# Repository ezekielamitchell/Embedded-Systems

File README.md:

# REDHAWK ESP32 Robot

Custom PCB-based robot designed and built for the Seattle University Embedded Systems & Design course. The board centers on an ESP32 microcontroller and includes motor drive, quadrature encoders, distance sensing, line following, ambient light sensing, audio output, and Wi-Fi. This repository contains the full KiCad hardware design, power-on functional test firmware, and supporting documentation.

---

## Repository Structure

```
Embedded-Systems/
├── Mitchel_Ezekiel_Robot/       # KiCad PCB and schematic project
├── PowerOn_Functional_Test/     # PlatformIO firmware — hardware self-test
└── Interrupts/                  # Interrupt lab (placeholder)
```

---

## PCB Design

KiCad 9.0 project containing the full schematic and two-layer PCB layout.

```
Mitchel_Ezekiel_Robot/
├── Mitchel_Ezekiel_Robot.kicad_pcb
├── Mitchel_Ezekiel_Robot.kicad_sch
├── Mitchel_Ezekiel_Robot.kicad_pro
├── Mitchel_Ezekiel_Robot.kicad_prl
├── Ezekiel_Mitchell_ESP32_Robot_Schematic.kicad_pro
├── sym-lib-table
├── docs/
│   ├── ESP32EmeddedRobot_Design-GetStarted-v00-1-10-2025a.pdf
│   └── images/
├── deliverables/
│   └── Ezekiel_Mitchell_ESP32_Robot_Schematic.kicad_sch
└── downloadables/
    ├── 0-My_Library.kicad_sym
    └── 0-My-Library.pretty/
```

### Hardware Overview

#### Microcontroller

| Part | Description |
|------|-------------|
| ESP32-DEVKITC-32E (U1) | Main MCU — dual-core Xtensa LX6, Wi-Fi + Bluetooth |

#### Motor Drive

| Part | Description |
|------|-------------|
| L293D (U3) | Dual H-bridge motor driver (DIP-16) |
| Pololu-3675 | Gear motors with quadrature encoders (x2) |
| Pololu-2691 / Ball-Caster-1 | Ball caster (rear support) |

#### Sensors and I/O

| Part | Description |
|------|-------------|
| R7 — R_Photo | LDR photoresistor (ambient light sensing) |
| D2 — LD274 | IR LED emitter (line detection) |
| Q1 — SFH300 | IR phototransistor receiver |
| HC-SR04 | Ultrasonic distance sensor (TRIG / ECHO) |
| HORN1 — Buzzer | Audio feedback (TDK PS1240P02BT) |
| D1, D3-D6 — LED | Status indicator LEDs (x5, 3 mm) |
| SW1 — SW_SPST | Tactile on/off switch |

#### Communication and Debug

| Part | Description |
|------|-------------|
| J2 — GPS MODULE | GPS module connector (UART: GPS_TX / GPS_RX) |
| J1 — JTAG | 1.27 mm 2x5 JTAG/SWD debug header |

#### Connectors

| Ref | Value | Description |
|-----|-------|-------------|
| J3 | Barrel_Jack_Switch | Battery input (horizontal barrel jack) |
| J4 | Conn_01x06 | General 6-pin header |
| J5 | Conn_01x06 | General 6-pin header |
| J6 | Conn_01x04 | General 4-pin header |
| J7 | Conn_02x03_Odd_Even | Motor / encoder connector (2x3) |

#### Passives and Power

| Ref | Value | Notes |
|-----|-------|-------|
| C1, C5-C7 | 0.1 uF | Decoupling capacitors |
| C2, C3 | 47 uF | Bulk filter capacitors |
| R1, R2 | 1 kOhm | Pull-up / current limiting |
| R3 | 47 kOhm | Pull-up for IR receiver circuit |
| R4, R5 | 330 Ohm | LED current limiting |
| R6 | 10 kOhm | Voltage divider (LDR / sensor bias) |

Power rails: `+BATT` (battery input), `+3V3` (regulated 3.3 V from ESP32 module)

### PCB Net Classes

| Net Class | Track Width | Via Diameter | Via Drill | Notes |
|-----------|-------------|--------------|-----------|-------|
| Power | 0.5 mm | 1.0 mm | 0.5 mm | VCC, GND rails |
| Motor | 0.8 mm | 1.2 mm | 0.6 mm | H-bridge output lines |
| High Speed / GPS | 0.2 mm | 0.8 mm | 0.4 mm | GPS UART, high-frequency signals |
| Default | 0.2 mm | 0.8 mm | 0.3 mm | General signals |

### Custom Libraries

Symbol library: `downloadables/0-My_Library.kicad_sym`
Footprint library: `downloadables/0-My-Library.pretty/`

Included footprints:

- `MODULE_ESP32-DEVKITC-32E`
- `Pololu-3675-GearMotorWEncoder`
- `Pololu-2691-Ball_Caster` / `Ball-Caster-1`
- `Basic-Robot-Outline_1`
- ECE capacitive and piano touch switch footprints
- `BAT_2481`, `TRIM_PTA3043-2015DPA104`, and others

### Getting Started (PCB)

1. Install [KiCad 9.0](https://www.kicad.org/)
2. Clone this repository
3. Open `Mitchel_Ezekiel_Robot/Mitchel_Ezekiel_Robot.kicad_pro` in KiCad
4. Register the custom libraries in KiCad's library manager:
   - Footprint: `downloadables/0-My-Library.pretty`
   - Symbol: `downloadables/0-My_Library.kicad_sym`
5. Refer to `docs/ESP32EmeddedRobot_Design-GetStarted-v00-1-10-2025a.pdf` for the original design brief

---

## Power-On Functional Test Firmware

PlatformIO/Arduino firmware that exercises every major peripheral in a fixed sequential test sequence. Flash once and observe the serial monitor for pass/fail output. Tests run in `setup()`; `loop()` serves the Wi-Fi web control interface.

```
PowerOn_Functional_Test/
├── platformio.ini       # PlatformIO config (espressif32 >= 6.0.0)
└── src/
    ├── config.h         # Pin definitions, PWM parameters, Wi-Fi credentials
    ├── main.cpp         # Test sequence and hardware helpers
    ├── web_control.h    # Web server public API
    └── web_control.cpp  # HTTP route handlers and web control page
```

### Prerequisites

| Requirement | Details |
| ----------- | ------- |
| PlatformIO | [platformio.org](https://platformio.org) or VS Code extension |
| ESP32-DevKitC | Connected via USB |
| Arduino-ESP32 core v3.x | Pulled in automatically by `espressif32@^6.0.0` |
| Assembled robot PCB | Motors, LEDs, horn, and sensors populated |

### Pin Map

| Signal | GPIO | Notes |
| ------ | ---- | ----- |
| Right Motor 1A / 2A | 18, 19 | L293D direction pins |
| Right Motor EN1 (PWM) | 26 | L293D enable — speed control |
| Left Motor 3A / 4A | 16, 17 | L293D direction pins |
| Left Motor EN3 (PWM) | 25 | L293D enable — speed control |
| Right Encoder A / B | 36, 39 | Input-only GPIOs, INPUT_PULLUP |
| Left Encoder A / B | 34, 35 | Input-only GPIOs, INPUT_PULLUP |
| Horn (piezo) | 21 | PWM — 1 kHz, 50% duty |
| Front LEDs | 2 | Bootstrap pin, safe as output after boot |
| Rear LEDs | 0 | Bootstrap pin, safe as output after boot |
| Photoresistor | 33 | ADC1_CH5 — 12-bit analog input |
| IR Line Sensor | 32 | Digital input |
| Ultrasonic TRIG / ECHO | 4, 27 | HC-SR04 |
| Status LED | 5 | Blinks during Wi-Fi connect, solid when connected |

### Test Sequence

| # | Test | Description | Pass Criteria |
|---|------|-------------|---------------|
| 1 | Horn | 5 slow beeps (400 ms on / 300 ms off) | Audible beeps |
| 2 | Front LEDs | 5 blinks on GPIO 2 | Visible flashes |
| 3 | Rear LEDs | 5 blinks on GPIO 0 | Visible flashes |
| 4 | Left Motor | Forward at 100% duty for 1 s | Wheel spins |
| 5 | Right Motor | Forward at 100% duty for 1 s | Wheel spins |
| 6 | Ultrasonic | 5 distance readings via HC-SR04 | At least one valid echo |
| 7 | IR / Line Sensor | Waits up to 10 s for signal transition (user interaction) | Transition detected |
| 8 | Photoresistor | 60 s day/night monitor — lamps follow light level (user interaction) | Lamps respond |
| 9 | Completion | 15 fast beeps as end-of-test signal | Audible beeps |
| EC | Wi-Fi + Web Server | Connects to configured SSID; starts HTTP control page | IP printed to serial |

Tests 7 and 8 require manual interaction. Listen for the two-beep prompt before covering or uncovering the respective sensor.

The web control page (extra credit) is served at the board's IP address after Wi-Fi connects. It displays test results and provides buttons to trigger the horn, toggle LEDs, and drive the motors.

### Build and Flash

Set Wi-Fi credentials in `src/config.h` before flashing:

```cpp
#define WIFI_SSID "your-network-name"
#define WIFI_PASS "your-password"
```

```bash
pio run                   # build
pio run --target upload   # build and flash
pio device monitor        # serial monitor at 115200 baud
```

VS Code: use the PlatformIO toolbar — Build, Upload, Monitor.

---

## Author

Ezekiel Mitchell — Seattle University, Embedded Systems & Design

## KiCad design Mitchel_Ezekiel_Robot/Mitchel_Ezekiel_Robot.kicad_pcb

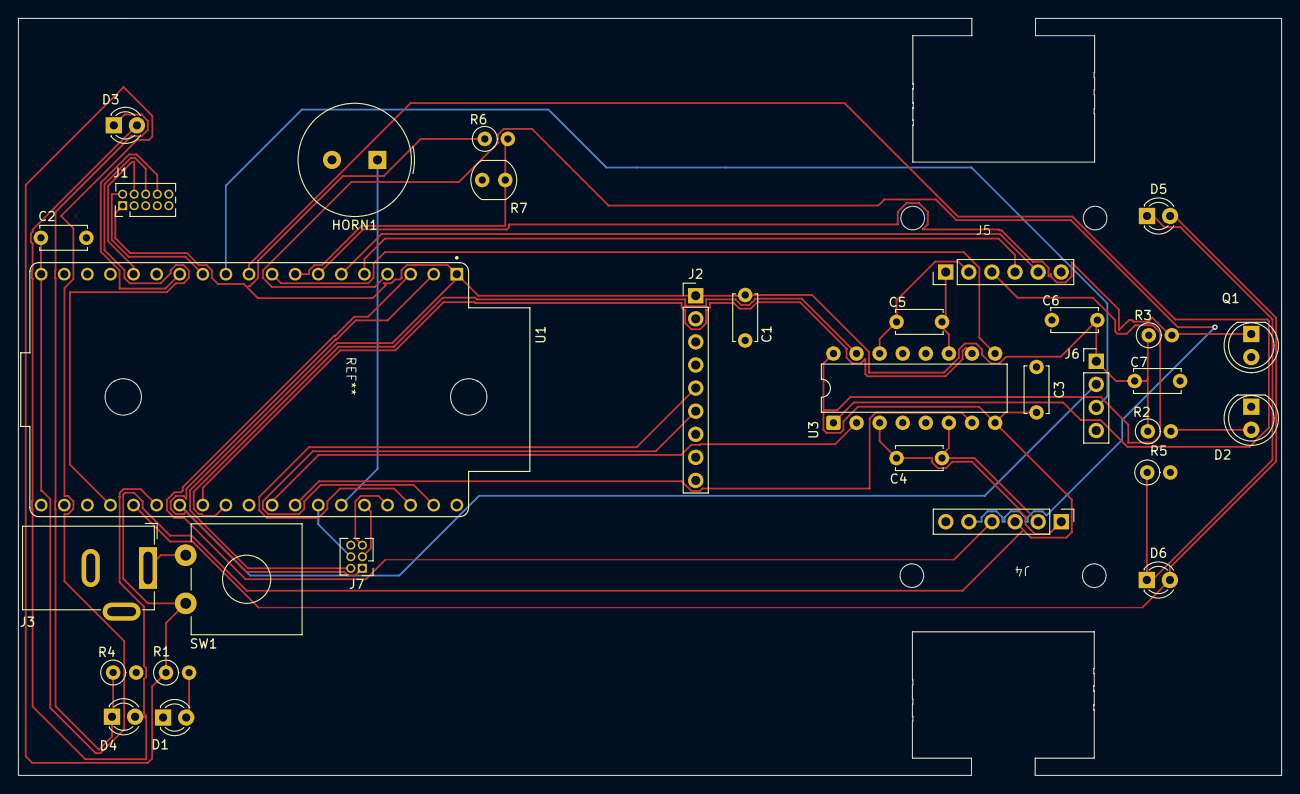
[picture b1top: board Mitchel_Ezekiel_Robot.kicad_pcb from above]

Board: 2 copper layers, 138.9 x 83.3 mm, 32 parts (0 on the bottom side), 38 nets.

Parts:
C1, C7: 0.1uF; C_Disc_D5.0mm_W2.5mm_P5.00mm
C2, C3: 47uF; C_Disc_D5.0mm_W2.5mm_P5.00mm
C4, C5, C6: 0.1Uf; C_Disc_D5.0mm_W2.5mm_P5.00mm
D1, D3, D4, D5, D6: LED; LED_D3.0mm
D2: LD274; LED_D5.0mm_IRGrey
HORN1: Buzzer; Buzzer_TDK_PS1240P02BT_D12.2mm_H6.5mm
J1: JTAG; PinHeader_2x05_P1.27mm_Vertical
J2: GPS MODULE; PinHeader_1x09_P2.54mm_Vertical
J3: Barrel_Jack_Switch; BarrelJack_GCT_DCJ200-10-A_Horizontal
J4, J5: Conn_01x06; Pololu-3675-GearMotorWEncoder
J6: Conn_01x04; PinHeader_1x04_P2.54mm_Vertical
J7: Conn_02x03_Odd_Even; PinHeader_2x03_P1.27mm_Vertical
Q1: SFH300; LED_D5.0mm_Clear
R1: 1k; R_Axial_DIN0207_L6.3mm_D2.5mm_P2.54mm_Vertical
R2: 1K; R_Axial_DIN0207_L6.3mm_D2.5mm_P2.54mm_Vertical
R3: 47K; R_Axial_DIN0207_L6.3mm_D2.5mm_P2.54mm_Vertical
R4, R5: 330; R_Axial_DIN0207_L6.3mm_D2.5mm_P2.54mm_Vertical
R6: 10K; R_Axial_DIN0207_L6.3mm_D2.5mm_P2.54mm_Vertical
R7: R_Photo; R_LDR_4.9x4.2mm_P2.54mm_Vertical
SW1: SW_SPST; SW_CW_GPTS203211B
U1: ESP32-DEVKITC-32E; MODULE_ESP32-DEVKITC-32E
U3: L293D; DIP-16_W7.62mm

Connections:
+3V3: C1.1, C6.2, C7.1, J1.1, J2.1, J6.1, J7.2, R2.1, R3.1, R6.1, U1.J2_1 (3V3)
+BATT: C2.1, C3.1, J4.3, J5.3, R1.1, SW1.2 (B), U1.J2_19 (EXT_5V), U3.8 (VCC2), U3.16 (VCC1)
/DAYNIGHT: R6.2, R7.1, U1.J2_8 (GPIO33,_ADC1_CH5,_TOUCH_CH8)
/ECHO: J6.3, U1.J2_11 (GPIO27,_ADC2_CH7,_TOUCH_CH7)
/FRONTLAMPS: D5.2 (A), D6.2 (A), U1.J3_15 (GPIO2,_ADC2_CH2,_TOUCH_CH2)
/GPS_RX: J2.6, U1.J3_2 (GPIO23)
/GPS_TX: J2.5, U1.J3_3 (GPIO22)
/HORN: HORN1.1 (+), U1.J3_6 (GPIO21)
/JTAG_MTCK: J1.4, U1.J2_15 (GPIO13,_ADC2_CH4,_TOUCH_CH4,_MTCK)
/JTAG_MTDI: J1.8, U1.J2_13 (GPIO12,_ADC2_CH5,_TOUCH_CH5,_MTDI)
/JTAG_MTDO: J1.6, U1.J3_16 (GPIO15,_ADC2_CH3,_TOUCH_CH3,_MTDO)
/JTAG_MTMS: J1.2, U1.J2_12 (GPIO14,_ADC2_CH6,_TOUCH_CH6,_MTMS)
/LENCODER_A: J5.4, U1.J2_5 (GPIO34,_ADC1_CH6,_VDET_1)
/LENCODER_B: J5.5, U1.J2_6 (GPIO35,_ADC1_CH7,_VDET_2)
/LMOTOR_3A: U1.J3_12 (GPIO16), U3.10 (3A)
/LMOTOR_4A: U1.J3_11 (GPIO17), U3.15 (4A)
/LPWM_3A4A: U1.J2_9 (GPIO25,_ADC1_CH8,_DAC_1), U3.9 (EN3,4)
/PHOTOTRANS: Q1.1 (C), R3.2, U1.J2_7 (GPIO32,_ADC1_CH4,_TOUCH_CH9)
/REARLAMPS: D3.2 (A), D4.2 (A), U1.J3_14 (GPIO0,_ADC2_CH1,_TOUCH_CH1,_Boot)
/RENCODER_A: J4.4, U1.J2_3 (GPIO36,_ADC1_CH0,_S_VP)
/RENCODER_B: J4.5, U1.J2_4 (GPIO39,_ADC1_CH3,_S_VN)
/RESET: J7.1, U1.J2_2 (CHIP_PU,_Reset)
/RMOTOR_1A: U1.J3_9 (GPIO18), U3.2 (1A)
/RMOTOR_2A: U1.J3_8 (GPIO19), U3.7 (2A)
/RPWM_1A2A: U1.J2_10 (GPIO26,_ADC2_CH9,_DAC_2), U3.1 (EN1,2)
/RXD: J7.5, U1.J3_4 (GPIO1,_U0TXD)
/TRIG: J6.2, U1.J3_13 (GPIO4,_ADC2_CH0,_TOUCH_CH0)
/TXD: J7.3, U1.J3_5 (GPIO3,_U0RXD)
GND: C1.2, C2.2, C3.2, C6.1, C7.2, D1.1 (K), D2.1 (K), HORN1.2 (-), J1.3, J1.5, J1.7, J1.9, J2.7, J3.2, J4.6, J5.6, J6.4, J7.4, Q1.2 (E), R4.2, R5.2, R7.2, U1.J2_14 (GND), U1.J3_1 (GND), U1.J3_7 (GND), U3.4 (GND), U3.5 (GND), U3.12 (GND), U3.13 (GND)
unnamed: D1.2 (A), R1.2
unnamed: D2.2 (A), R2.2
unnamed: D3.1 (K), D4.1 (K), R4.1
unnamed: D5.1 (K), D6.1 (K), R5.1
unnamed: C4.1, J4.1, U3.3 (1Y)
unnamed: C4.2, J4.2, U3.6 (2Y)
unnamed: C5.1, J5.1, U3.11 (3Y)
unnamed: C5.2, J5.2, U3.14 (4Y)
unnamed: J3.1, SW1.1 (A)

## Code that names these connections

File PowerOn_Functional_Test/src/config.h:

#pragma once

// Right motor (L293D EN1 / 1A / 2A)
#define RMOTOR_1A 18
#define RMOTOR_2A 19
#define RPWM_1A2A 26

// Left motor (L293D EN3 / 3A / 4A)
#define LMOTOR_3A 16
#define LMOTOR_4A 17
#define LPWM_3A4A 25

// Encoders - quadrature, open-drain, INPUT_PULLUP required
#define RENCODER_A 36
#define RENCODER_B 39
#define LENCODER_A 34
#define LENCODER_B 35

// Horn
#define HORN 21

// Lighting
#define FRONTLAMPS 2
#define REARLAMPS 0

// Sensors
#define DAYNIGHT 33
#define IR_RECEIVE 32

// Ultrasonic (HC-SR04) — TRIG=4, ECHO=27
// Wiring: VCC → 5 V, GND → GND, TRIG → GPIO 4, ECHO → GPIO 27
#define TRIG 4
#define ECHO 27

// Status LED
#define STATUS_LED 5

// PWM parameters
#define HORN_FREQ 1000
#define HORN_RES 8
#define HORN_DUTY 128

#define MOTOR_FREQ 5000
#define MOTOR_RES 8
#define MOTOR_FULL_DUTY 255

#define HORN_CH 0
#define RMOTOR_CH 1
#define LMOTOR_CH 2

// Wi-Fi credentials (station mode - not used when running as soft AP)
#define WIFI_SSID "SU-ECE-LAB"
#define WIFI_PASS "FaraDay8086!"


// Access point credentials (ESP32 hosts the network)
#define AP_SSID "ezekielRobot"
#define AP_PASS "password123"  // leave empty for open network

// Autonomous mode tuning

// Line sensor polarity: 0 = LOW over line, 1 = HIGH over line
#define LINE_DETECT_LEVEL  0

// Motor duty cycles (0-255)
#define SPEED_SLOW 140
#define SPEED_MED 180
#define SPEED_FAST 220
#define SPEED_TURN 155

// Maze solver
#define MAZE_SPEED SPEED_FAST
#define WALL_STOP_CM 18    // stop & turn when obstacle ≤ this
#define TURN_90_MS 430    // time for ~90° pivot at SPEED_TURN

// Line sensor analog threshold
// Sensor outputs HIGHER analog values over black tape (tape absorbs IR, transistor conducts less).
// Readings above this value are treated as "on line".
// Tune by running test 5 and observing on-tape vs off-tape analog values.
#define LINE_SENSOR_THRESHOLD  650

// Line follower (single IR sensor — bang-bang edge tracking)
#define LINE_FOLLOW_SPEED  SPEED_MED  // base drive speed while following
#define LINE_INNER_RATIO   4          // inner-wheel divisor for gentle curves (1=pivot, 2=moderate, 4=gentle)

// Web watchdog: stop motors if no /drive command within this window (ms)
#define WEB_WATCHDOG_MS 600

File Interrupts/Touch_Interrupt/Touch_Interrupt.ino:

/*
  Touch Interrupt - Capacitive Touch Detection
  Valid touch-capable pins: GPIO 0, 2, 3, 12, 13, 14, 15, 27, 32, 33

  Touching a wire/foil pad connected to GPIO 27 toggles an LED on GPIO 26.
  The ESP32's capacitive touch sensor measures charge/discharge time;
  a lower reading means touch detected.

  Wiring:
    - Touch pad: a short wire or piece of aluminium foil on GPIO 27
    - LED: anode to GPIO 26 through 330Ω resistor, cathode to GND
*/

#define TOUCH_PIN  T7   // GPIO 27  (T0=GPIO4, T2=GPIO2, T3=GPIO15,
                        //           T4=GPIO13, T5=GPIO12, T6=GPIO14,
                        //           T7=GPIO27, T8=GPIO33, T9=GPIO32)
#define LED_PIN    26

volatile bool ledState   = false;
volatile bool touchFlag  = false;

// ISR called when touch threshold is crossed
void IRAM_ATTR touchISR() {
  touchFlag = true;
}

void setup() {
  Serial.begin(115200);

  pinMode(LED_PIN, OUTPUT);
  digitalWrite(LED_PIN, LOW);

  // Attach touch interrupt: fires when sensor value drops below threshold (40)
  // Lower threshold = less sensitive; raise if false-triggers
  touchAttachInterrupt(TOUCH_PIN, touchISR, 40);

  Serial.println("Touch Interrupt ready. Touch GPIO 27 pad to toggle LED.");
}

void loop() {
  if (touchFlag) {
    touchFlag = false;
    ledState  = !ledState;
    digitalWrite(LED_PIN, ledState ? HIGH : LOW);

    Serial.print("Touch detected! LED: ");
    Serial.println(ledState ? "ON" : "OFF");
    Serial.print("Raw touch value: ");
    Serial.println(touchRead(TOUCH_PIN));

    delay(300); // simple debounce — touch pads tend to ring
  }
}

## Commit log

2026-01-09 init
2026-01-09 mitchell robot 1 completion
2026-01-20 back from vacation
    what's going on?
2026-01-20 Robot Car Schematic Completion
    Complete schematic for robotic car
2026-01-20 Add robot outline footprint to PCB design
    Added the 'Basic-Robot-Outline_1' footprint to Mitchel_Ezekiel_Robot.kicad_pcb, including edge cuts and fabrication details. Updated backup files to reflect the latest PCB changes and removed outdate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
2026-01-21 Update PCB layout and add new backup files
    Added four new backup ZIP files. Updated component placements and properties in Mitchel_Ezekiel_Robot.kicad_pcb, including changes to footprints, positions, and silkscreen details. Removed autosave a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
2026-01-21 gerber complete -- maybe...
2026-01-21 done
2026-02-24 pcb stage + images
2026-02-25 pcb edit
2026-02-25 Clarify KiCad usage in project description
    Updated description to clarify the use of KiCad.
2026-02-25 readme update
2026-02-25 complete
2026-02-26 pcb gnd short fix
2026-02-26 update pcb edit
2026-02-26 caster insert
2026-02-26 readme fix
2026-03-02 coded bot
2026-03-11 functionality tests
2026-03-11 functions doc
2026-03-11 fix test plan - config
2026-03-11 time update
2026-03-11 robot wifi + ip
2026-03-11 change wifi to local + fix led off timing issue
2026-03-13 line following test
2026-03-13 dance part
2026-03-13 remove auto light detection
2026-03-13 error in line folloing
2026-03-15 remove line following function -- bug overload
2026-03-15 watchdog - threshold bar - line error
2026-03-16 watchdog
2026-03-16 line follow fix
2026-03-16 line follow bug fix
2026-03-16 manual bug fix
2026-03-19 maze + dance update
2026-03-19 robot complete
2026-03-24 robo-compelte
